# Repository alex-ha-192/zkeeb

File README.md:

# zkeeb
A low-profile custom wireless mechanical keyboard based on the ZMK keyboard firmware

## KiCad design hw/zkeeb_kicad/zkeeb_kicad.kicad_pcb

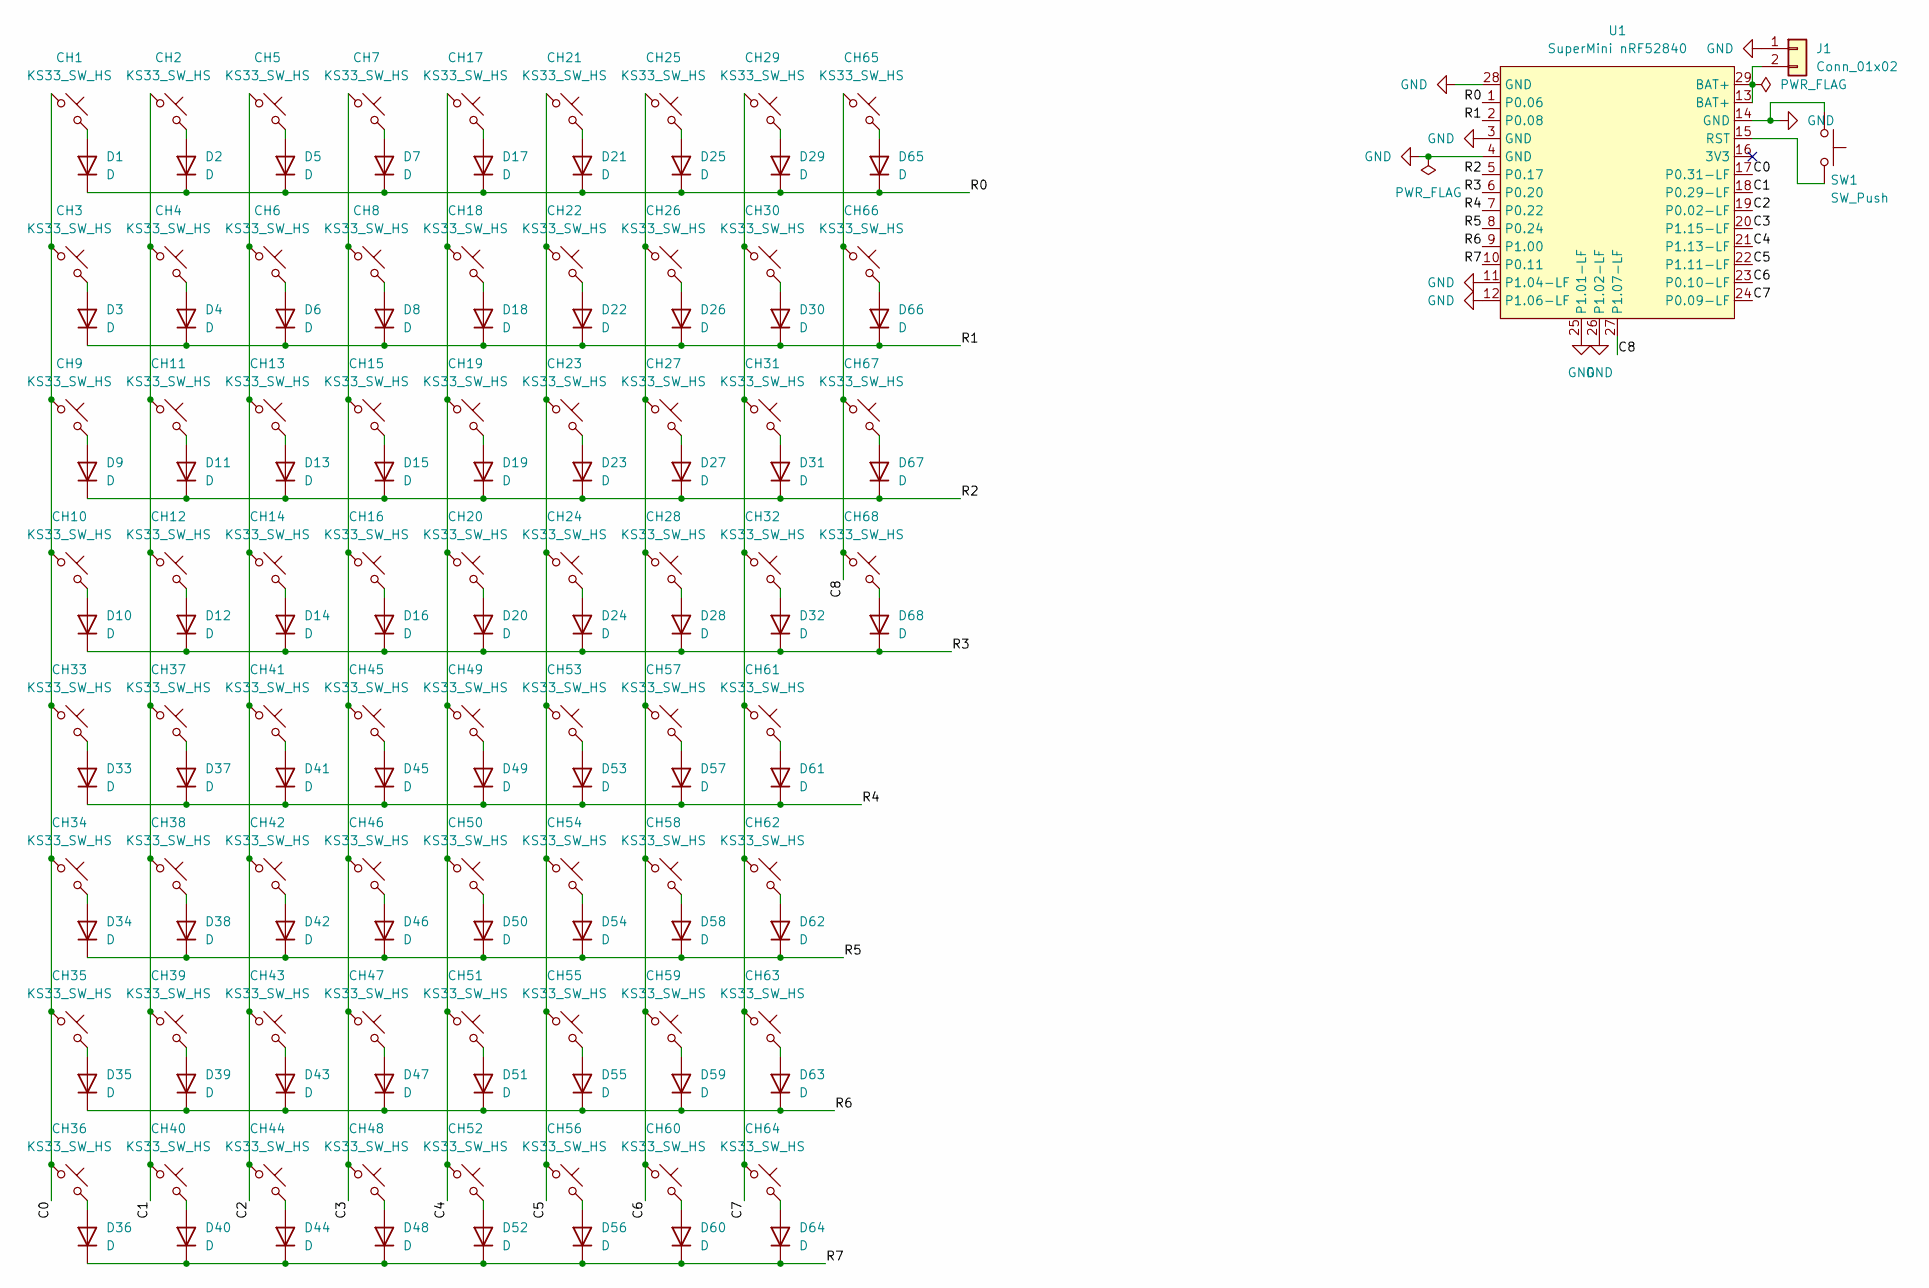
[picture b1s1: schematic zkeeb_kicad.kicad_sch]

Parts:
CH1, CH2, CH3, CH4, CH5, CH6, CH7, CH8, CH9, CH10, CH11, CH12, CH13, CH14, CH15, CH16, CH17, CH18, CH19, CH20, CH21, CH22, CH23, CH24, CH25, CH26, CH27, CH28, CH29, CH30, CH31, CH32, CH33, CH34, CH35, CH36, CH37, CH38, CH39, CH40, CH41, CH42, CH43, CH44, CH45, CH46, CH47, CH48, CH49, CH50, CH51, CH52, CH53, CH54, CH55, CH56, CH57, CH58, CH59, CH60, CH61, CH62, CH63, CH64, CH65, CH66, CH67, CH68: KS33_SW_HS; Gateron-KS33-Hotswap-1U
D1, D2, D3, D4, D5, D6, D7, D8, D9, D10, D11, D12, D13, D14, D15, D16, D17, D18, D19, D20, D21, D22, D23, D24, D25, D26, D27, D28, D29, D30, D31, D32, D33, D34, D35, D36, D37, D38, D39, D40, D41, D42, D43, D44, D45, D46, D47, D48, D49, D50, D51, D52, D53, D54, D55, D56, D57, D58, D59, D60, D61, D62, D63, D64, D65, D66, D67, D68: D; D_SOD-123
J1: Conn_01x02; JST_PH_B2B-PH-K_1x02_P2.00mm_Vertical
SW1: SW_Push; SW_SKSCLCE010_AAL
U1: SuperMini nRF52840; SuperMini_nRF52840_AH_USBup

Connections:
/C0: CH1.1, CH3.1, CH9.1, CH10.1, CH33.1, CH34.1, CH35.1, CH36.1, U1.17 (P0.31-LF)
/C1: CH2.1, CH4.1, CH11.1, CH12.1, CH37.1, CH38.1, CH39.1, CH40.1, U1.18 (P0.29-LF)
/C2: CH5.1, CH6.1, CH13.1, CH14.1, CH41.1, CH42.1, CH43.1, CH44.1, U1.19 (P0.02-LF)
/C3: CH7.1, CH8.1, CH15.1, CH16.1, CH45.1, CH46.1, CH47.1, CH48.1, U1.20 (P1.15-LF)
/C4: CH17.1, CH18.1, CH19.1, CH20.1, CH49.1, CH50.1, CH51.1, CH52.1, U1.21 (P1.13-LF)
/C5: CH21.1, CH22.1, CH23.1, CH24.1, CH53.1, CH54.1, CH55.1, CH56.1, U1.22 (P1.11-LF)
/C6: CH25.1, CH26.1, CH27.1, CH28.1, CH57.1, CH58.1, CH59.1, CH60.1, U1.23 (P0.10-LF)
/C7: CH29.1, CH30.1, CH31.1, CH32.1, CH61.1, CH62.1, CH63.1, CH64.1, U1.24 (P0.09-LF)
/C8: CH65.1, CH66.1, CH67.1, CH68.1, U1.27 (P1.07-LF)
/R0: D1.1 (K), D2.1 (K), D5.1 (K), D7.1 (K), D17.1 (K), D21.1 (K), D25.1 (K), D29.1 (K), D65.1 (K), U1.1 (P0.06)
/R1: D3.1 (K), D4.1 (K), D6.1 (K), D8.1 (K), D18.1 (K), D22.1 (K), D26.1 (K), D30.1 (K), D66.1 (K), U1.2 (P0.08)
/R2: D9.1 (K), D11.1 (K), D13.1 (K), D15.1 (K), D19.1 (K), D23.1 (K), D27.1 (K), D31.1 (K), D67.1 (K), U1.5 (P0.17)
/R3: D10.1 (K), D12.1 (K), D14.1 (K), D16.1 (K), D20.1 (K), D24.1 (K), D28.1 (K), D32.1 (K), D68.1 (K), U1.6 (P0.20)
/R4: D33.1 (K), D37.1 (K), D41.1 (K), D45.1 (K), D49.1 (K), D53.1 (K), D57.1 (K), D61.1 (K), U1.7 (P0.22)
/R5: D34.1 (K), D38.1 (K), D42.1 (K), D46.1 (K), D50.1 (K), D54.1 (K), D58.1 (K), D62.1 (K), U1.8 (P0.24)
/R6: D35.1 (K), D39.1 (K), D43.1 (K), D47.1 (K), D51.1 (K), D55.1 (K), D59.1 (K), D63.1 (K), U1.9 (P1.00)
/R7: D36.1 (K), D40.1 (K), D44.1 (K), D48.1 (K), D52.1 (K), D56.1 (K), D60.1 (K), D64.1 (K), U1.10 (P0.11)
GND: J1.1, SW1.1, U1.3 (GND), U1.4 (GND), U1.11 (P1.04-LF), U1.12 (P1.06-LF), U1.14 (GND), U1.25 (P1.01-LF), U1.26 (P1.02-LF), U1.28 (GND)
unnamed: CH1.2, D1.2 (A)
unnamed: CH2.2, D2.2 (A)
unnamed: CH3.2, D3.2 (A)
unnamed: CH4.2, D4.2 (A)
unnamed: CH5.2, D5.2 (A)
unnamed: CH6.2, D6.2 (A)
unnamed: CH7.2, D7.2 (A)
unnamed: CH8.2, D8.2 (A)
unnamed: CH9.2, D9.2 (A)
unnamed: CH10.2, D10.2 (A)
unnamed: CH11.2, D11.2 (A)
unnamed: CH12.2, D12.2 (A)
unnamed: CH13.2, D13.2 (A)
unnamed: CH14.2, D14.2 (A)
unnamed: CH15.2, D15.2 (A)
unnamed: CH16.2, D16.2 (A)
unnamed: CH17.2, D17.2 (A)
unnamed: CH18.2, D18.2 (A)
unnamed: CH19.2, D19.2 (A)
unnamed: CH20.2, D20.2 (A)
unnamed: CH21.2, D21.2 (A)
unnamed: CH22.2, D22.2 (A)
unnamed: CH23.2, D23.2 (A)
unnamed: CH24.2, D24.2 (A)
unnamed: CH25.2, D25.2 (A)
unnamed: CH26.2, D26.2 (A)
unnamed: CH27.2, D27.2 (A)
unnamed: CH28.2, D28.2 (A)
unnamed: CH29.2, D29.2 (A)
unnamed: CH30.2, D30.2 (A)
unnamed: CH31.2, D31.2 (A)
unnamed: CH32.2, D32.2 (A)
unnamed: CH33.2, D33.2 (A)
unnamed: CH34.2, D34.2 (A)
unnamed: CH35.2, D35.2 (A)
unnamed: CH36.2, D36.2 (A)
unnamed: CH37.2, D37.2 (A)
unnamed: CH38.2, D38.2 (A)
unnamed: CH39.2, D39.2 (A)
unnamed: CH40.2, D40.2 (A)
unnamed: CH41.2, D41.2 (A)
unnamed: CH42.2, D42.2 (A)
unnamed: CH43.2, D43.2 (A)
unnamed: CH44.2, D44.2 (A)
unnamed: CH45.2, D45.2 (A)
unnamed: CH46.2, D46.2 (A)
unnamed: CH47.2, D47.2 (A)
unnamed: CH48.2, D48.2 (A)
unnamed: CH49.2, D49.2 (A)
unnamed: CH50.2, D50.2 (A)
unnamed: CH51.2, D51.2 (A)
unnamed: CH52.2, D52.2 (A)
unnamed: CH53.2, D53.2 (A)
unnamed: CH54.2, D54.2 (A)
unnamed: CH55.2, D55.2 (A)
unnamed: CH56.2, D56.2 (A)
unnamed: CH57.2, D57.2 (A)
unnamed: CH58.2, D58.2 (A)
unnamed: CH59.2, D59.2 (A)
unnamed: CH60.2, D60.2 (A)
unnamed: CH61.2, D61.2 (A)
unnamed: CH62.2, D62.2 (A)
unnamed: CH63.2, D63.2 (A)
unnamed: CH64.2, D64.2 (A)
unnamed: CH65.2, D65.2 (A)
unnamed: CH66.2, D66.2 (A)
unnamed: CH67.2, D67.2 (A)
unnamed: CH68.2, D68.2 (A)
unnamed: J1.2, U1.13 (BAT+), U1.29 (BAT+)
unnamed: SW1.2, U1.15 (RST)

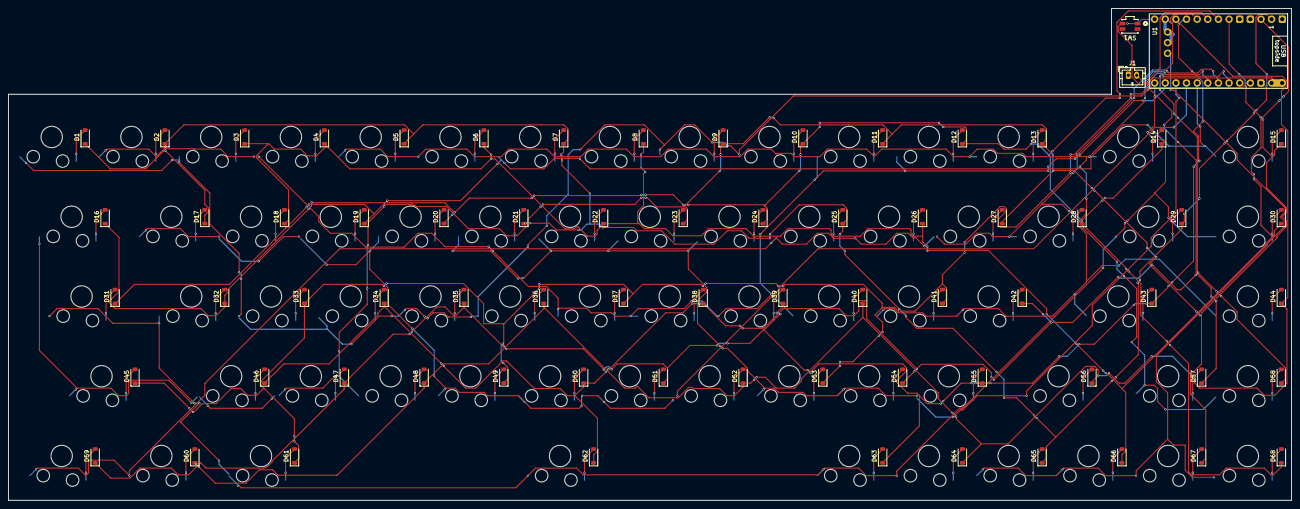
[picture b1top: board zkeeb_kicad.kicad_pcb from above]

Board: 2 copper layers, 306.5 x 117.5 mm, 139 parts (0 on the bottom side), 88 nets.
